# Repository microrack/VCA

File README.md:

# VCA
Voltage controlled amplifier for microrack

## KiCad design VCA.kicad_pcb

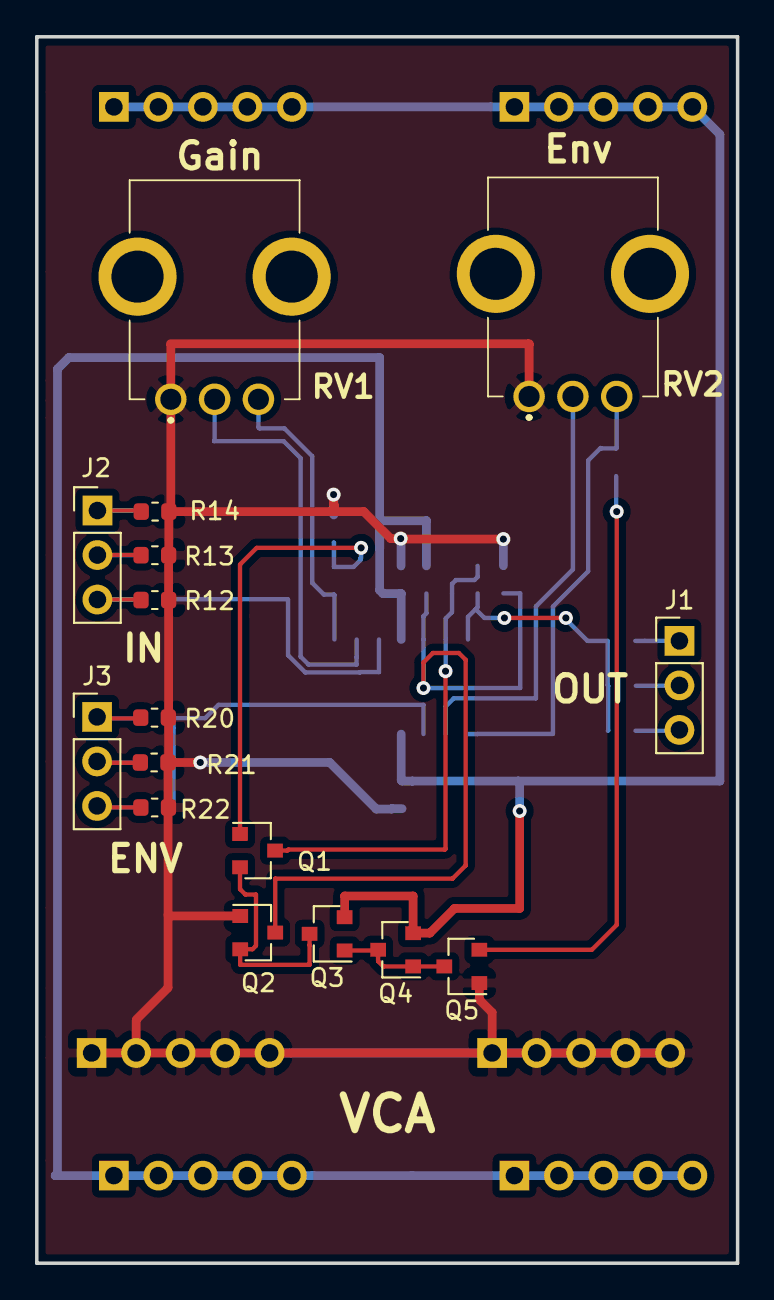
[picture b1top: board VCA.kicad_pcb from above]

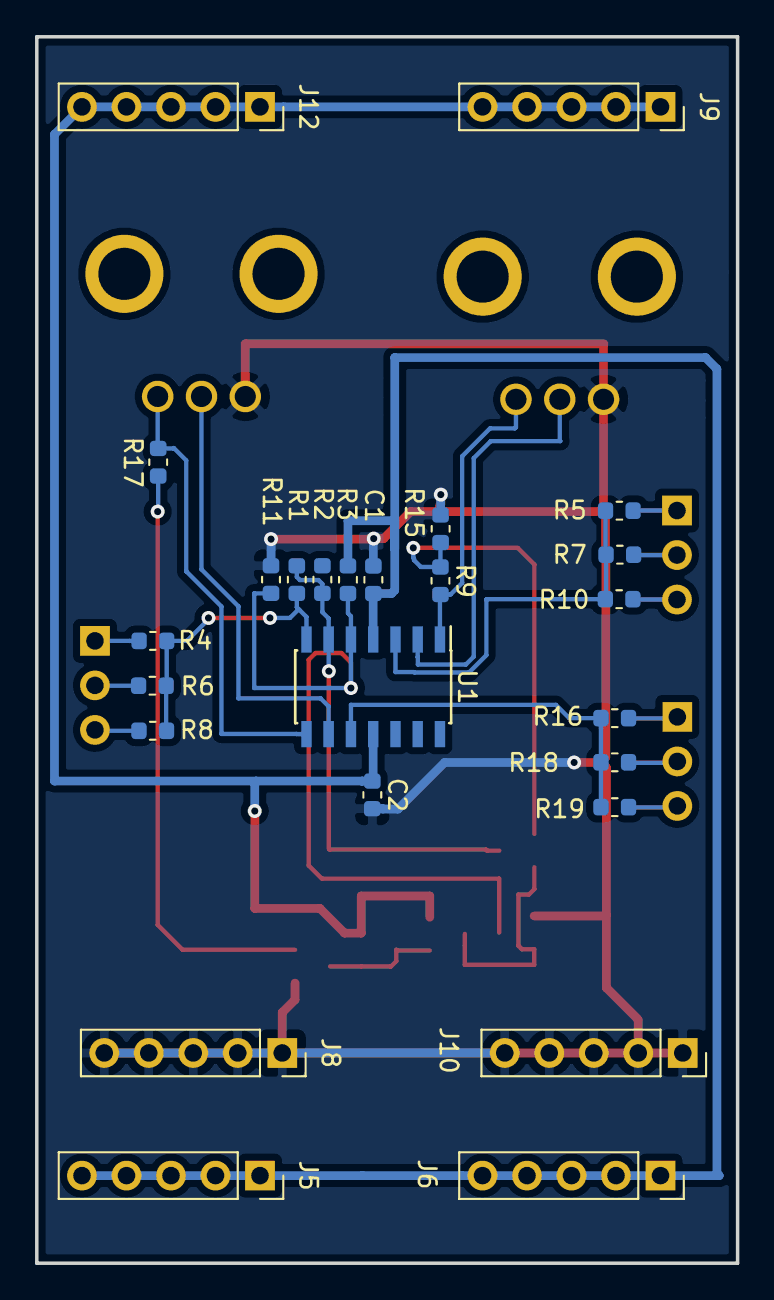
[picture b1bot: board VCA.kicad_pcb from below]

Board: 2 copper layers, 40.0 x 70.0 mm, 41 parts (25 on the bottom side), 25 nets.

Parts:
C1, C2: 0.1 uF; c0603
J1: Output; pls1x03
J2: Input; pls1x03
J3: Env; pls1x03
J5, J6, J8, J9, J10, J12: Conn_01x05_Male; pls1x05
Q1, Q2, Q3, Q4: BC817; SOT-23
Q5: BC807; SOT-23
R1, R5, R7, R10, R11, R16, R18, R19: 100K; r0603
R2, R3, R9, R17: 24K; r0603
R4, R6, R8, R15: 100R; r0603
R12, R13, R14, R20, R21, R22: 1K; r0603
RV1, RV2: 10K; R0904N
U1: LM324; soic-14

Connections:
+5V: C1.2, J5.1, J5.2, J5.3, J5.4, J5.5, J6.1, J6.2, J6.3, J6.4, J6.5, R2.1, R3.1, U1.4
-5V: C2.1, J9.1, J9.2, J9.3, J9.4, J9.5, J12.1, J12.2, J12.3, J12.4, J12.5, Q3.2, Q4.2, U1.11
/ENV_1: J3.1, R16.2, R20.1
/ENV_2: J3.2, R18.2, R21.1
/ENV_3: J3.3, R19.2, R22.1
/IN_2: J2.2, R7.2, R13.1
/IN_3: J2.3, R10.2, R12.1
GND: C1.1, C2.2, J8.1, J8.2, J8.3, J8.4, J8.5, J10.1, J10.2, J10.3, J10.4, J10.5, Q2.1, Q5.1, R11.2, R12.2, R13.2, R14.2, R15.2, R20.2, R21.2, R22.2, RV1.1, RV2.1
unnamed: J1.1, R4.1
unnamed: J1.2, R6.1
unnamed: J1.3, R8.1
unnamed: J2.1, R5.2, R14.1
unnamed: Q1.1, R9.1, R15.1
unnamed: Q1.2, Q2.2, Q3.3
unnamed: Q1.3, R1.2, R2.2, U1.6
unnamed: Q2.3, R3.2, R11.1, U1.5
unnamed: Q3.1, Q4.1, Q4.3, Q5.3
unnamed: Q5.2, R17.1
unnamed: R1.1, R4.2, R6.2, R8.2, U1.7
unnamed: R9.2, RV1.3, U1.1
unnamed: R5.1, R7.1, R10.1, U1.3
unnamed: R16.1, R18.1, R19.1, U1.10
unnamed: R17.2, RV2.3, U1.8
unnamed: RV1.2, U1.2
unnamed: RV2.2, U1.9

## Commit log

2019-04-05 Изменены УГО резисторов с европейского вида на Российский
2019-04-10 Плата 40х70 мм. Добавленны подписи компонентов и регуляторов Косметические изменения в схеме, уменьшенно количество разъемов питания
